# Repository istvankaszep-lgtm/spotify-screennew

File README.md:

# ESP32 Spotify Remote Controller

A custom ESP32-based hardware controller featuring an ILI9341 TFT display and a rotary encoder to wirelessly control Spotify playback over Wi-Fi.

## Quick start
1. Clone this repository and open the file in the `firmware` folder using Arduino IDE.
2. Install the required libraries (`TFT_eSPI`, `ESP32Encoder`, `SpotifyEsp32`).
3. Update your Wi-Fi credentials (`ssid`, `password`) and Spotify API credentials (`clientId`, `clientSecret`) in the code.
4. Upload the code to your ESP32 board and connect power via USB-C.

## Features
* **Spotify Integration:** Uses `SpotifyEsp32` to control playback (Next/Previous track, Play/Pause).
* **Rotary Encoder Controls:** Turn the knob (GPIO 25, 26) to skip tracks and press the button (GPIO 27) for play/pause.
* **TFT Display:** ILI9341 320x240 screen driven by `TFT_eSPI` for status and track updates.
* **Hardware:** Custom PCB with an ESP32-WROOM-32 module, USB-C interface, and onboard AMS1117 3.3V power regulation.

## How it works
The project runs on an ESP32-WROOM-32 microcontroller. Upon boot, it connects to Wi-Fi and initializes the ILI9341 display. The `ESP32Encoder` library handles the rotary encoder inputs to trigger Spotify API calls (`spotify.nextTrack()`, `spotify.previousTrack()`) over a secure Wi-Fi client (`WiFiClientSecure`).

## 💰 Bill of Materials (BOM)
"Id","Designator","Footprint","Quantity","Designation","Supplier_and_ref"
1,"U1","ESP32-WROOM-32",1,"ESP32-WROOM-32 SMD Module","Drot RO: https://www.drot.ro/platforma-arduino/2062-modul-esp-wroom-32-wifi-wlan-si-bluetooth.html"
2,"R2,R1","R_0805_2012Metric",2,"10k","Optimus Digital: https://www.optimusdigital.ro/ro/componente-electronice-rezistoare/638-set-de-rezistoare-smd-0805.html"
3,"C2","CP_Elec_5x5.4",1,"10uF","TME RO: https://www.tme.eu/ro/details/sc1h106m6l005vr/condensatoare-electrolitice-smd/samwha/"
4,"U3","SOT-223-3_TabPin2",1,"AMS1117-3.3","Sigmanortec: https://sigmanortec.ro/Modul-coborator-tensiune-AMS1117-3-3V-p134573098"
5,"SW1","RotaryEncoder_Alps_EC11E",1,"RotaryEncoder_Switch","Sigmanortec: https://sigmanortec.ro/Encoder-rotativ-cu-click-20mm-EC11-p128736611"
6,"P1","USB_C_Receptacle_HRO_TYPE-C-31-M-12",1,"USB_C_Plug_USB2.0","eMAG RO: https://www.emag.ro/conector-usb-tip-c-montare-pcb-smd-16-pin-tht-k684-um/pd/DNLXNRMBM/"
7,"C3,C1","C_0805_2012Metric",2,"100nF","TME RO: https://www.tme.eu/ro/details/cl21b104kacnnnc/condensatoare-mlcc-smd/samsung/"
8,"U2","CR2013-MI2120",1,"ILI9341_TFT","Optimus Digital: https://www.optimusdigital.ro/ro/optoelectronice-lcd-uri/3531-modul-lcd-de-24-cu-spi-i-controller-ili9341-240x320-px.html"

TOTAL (including printing on jplcpcb with "Global Standart Direct Line" shiping 12.39eur): 71.03eur

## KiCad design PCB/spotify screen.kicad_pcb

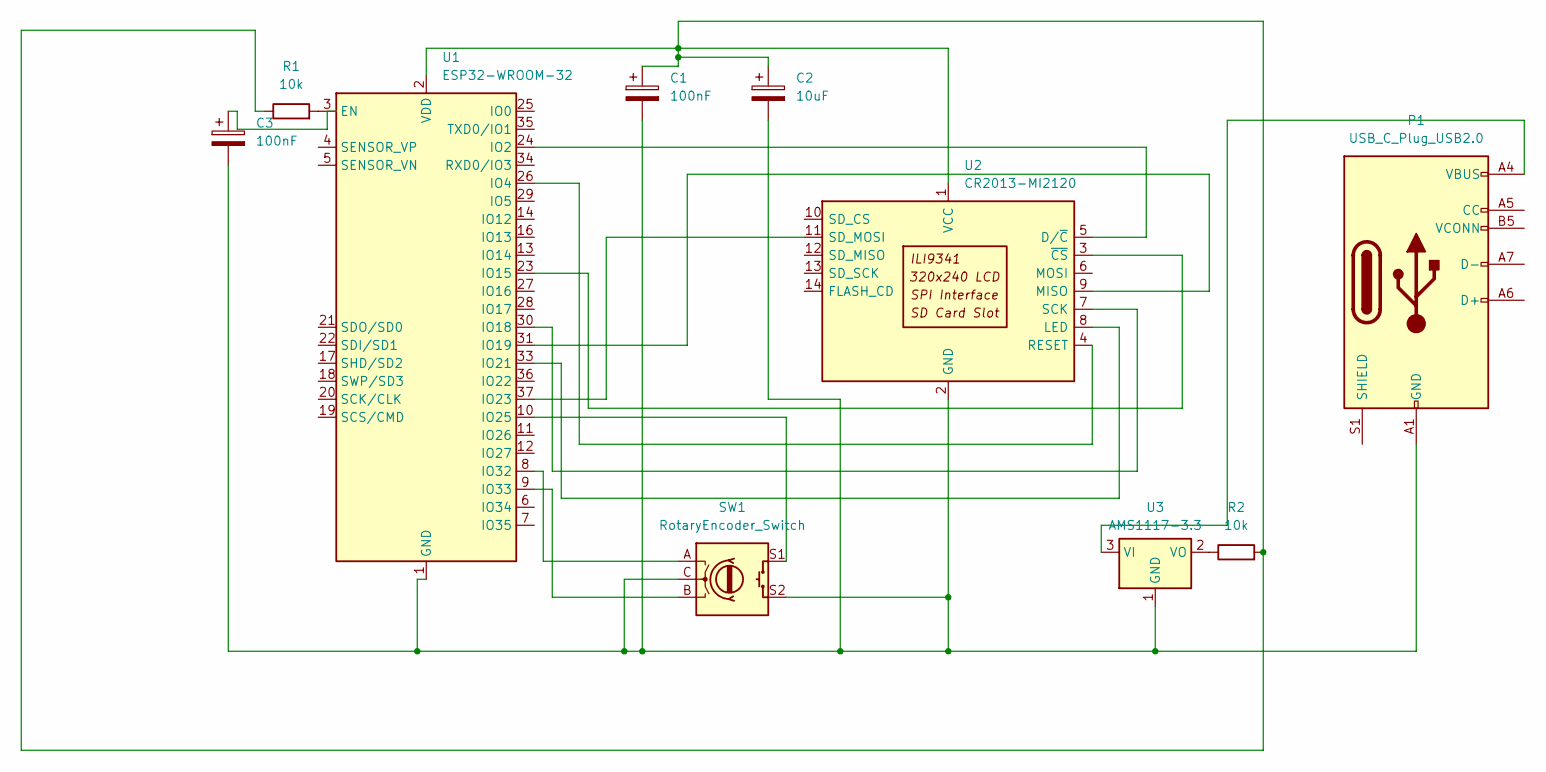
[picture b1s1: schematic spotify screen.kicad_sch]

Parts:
C1, C3: 100nF; C_0805_2012Metric
C2: 10uF; CP_Elec_5x5.4
P1: USB_C_Plug_USB2.0; USB_C_Receptacle_HRO_TYPE-C-31-M-12
R1, R2: 10k; R_0805_2012Metric
SW1: RotaryEncoder_Switch; RotaryEncoder_Alps_EC11E-Switch_Vertical_H20mm_CircularMoun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
U1: ESP32-WROOM-32
U2: CR2013-MI2120
U3: AMS1117-3.3; SOT-223-3_TabPin2

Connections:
unnamed: R1.2, U1.3 (EN)
unnamed: U1.24 (IO2), U2.5 (D/~C)
unnamed: U1.26 (IO4), U2.4 (RESET)
unnamed: U1.23 (IO15), U2.3 (~CS)
unnamed: U1.30 (IO18), U2.7 (SCK)
unnamed: U1.31 (IO19), U2.9 (MISO)
unnamed: U1.33 (IO21), U2.8 (LED)
unnamed: U1.37 (IO23), U2.11 (SD_MOSI)
unnamed: SW1.S1, U1.10 (IO25)
unnamed: SW1.A, U1.8 (IO32)
unnamed: SW1.B, U1.9 (IO33)
unnamed: C1.1, C2.1, R1.1, R2.2, U1.2 (VDD), U2.1 (VCC)
unnamed: C1.2, C2.2, C3.2, P1.A1 (GND), P1.A12 (GND), P1.B1 (GND), P1.B12 (GND), SW1.C, SW1.S2, U1.1 (GND), U1.15 (GND), U1.38 (GND), U1.39 (GND), U2.2 (GND), U3.1 (GND)
unnamed: P1.A4 (VBUS), P1.A9 (VBUS), P1.B4 (VBUS), P1.B9 (VBUS), U3.3 (VI)
unnamed: R2.1, U3.2 (VO)

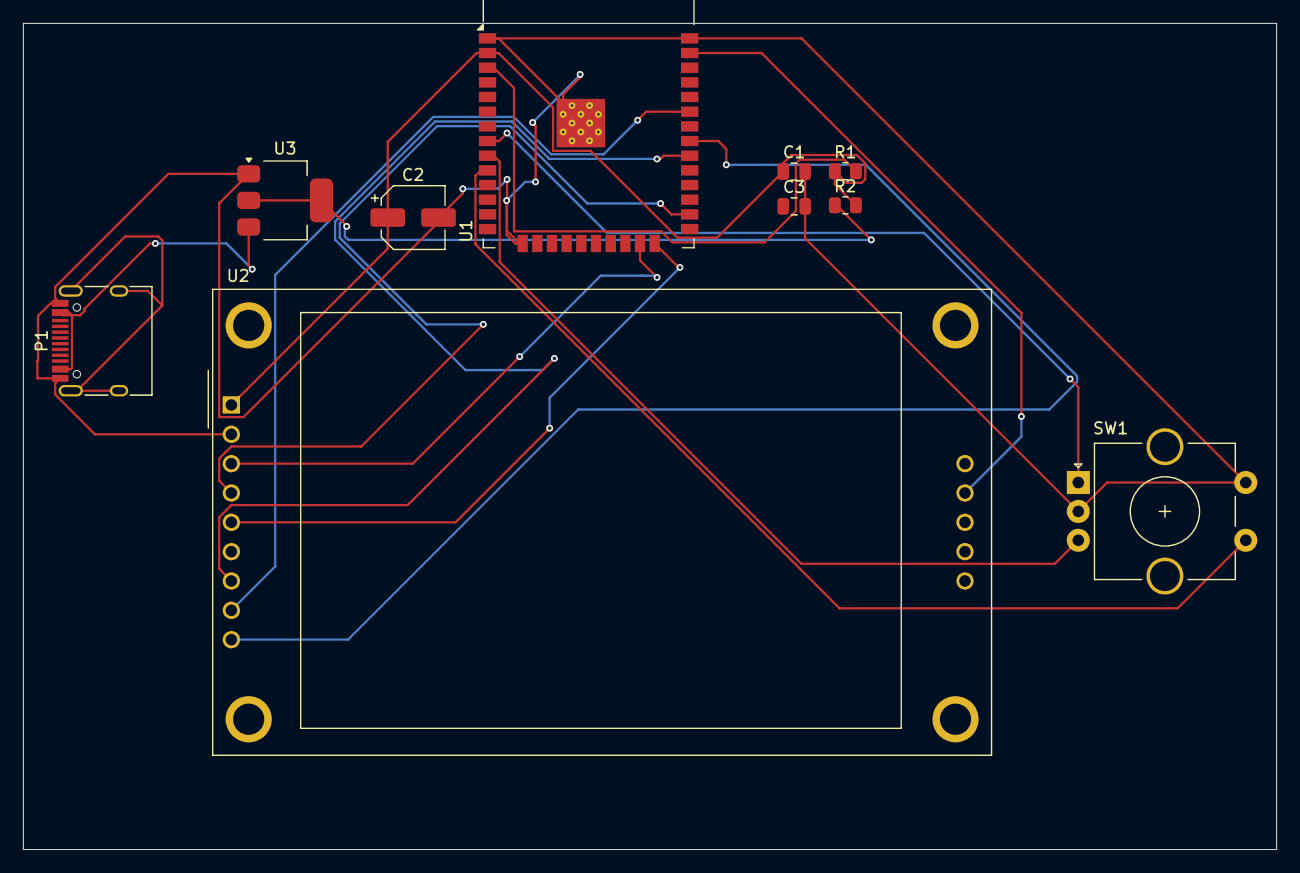
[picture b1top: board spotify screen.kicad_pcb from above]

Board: 2 copper layers, 108.5 x 71.5 mm, 10 parts (0 on the bottom side), 15 nets.
